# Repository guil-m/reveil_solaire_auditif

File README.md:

# Projet PCB FISE 5A POLYTECH
## Réveil solaire et auditif

### TO-DO List

- Poursuivre routing

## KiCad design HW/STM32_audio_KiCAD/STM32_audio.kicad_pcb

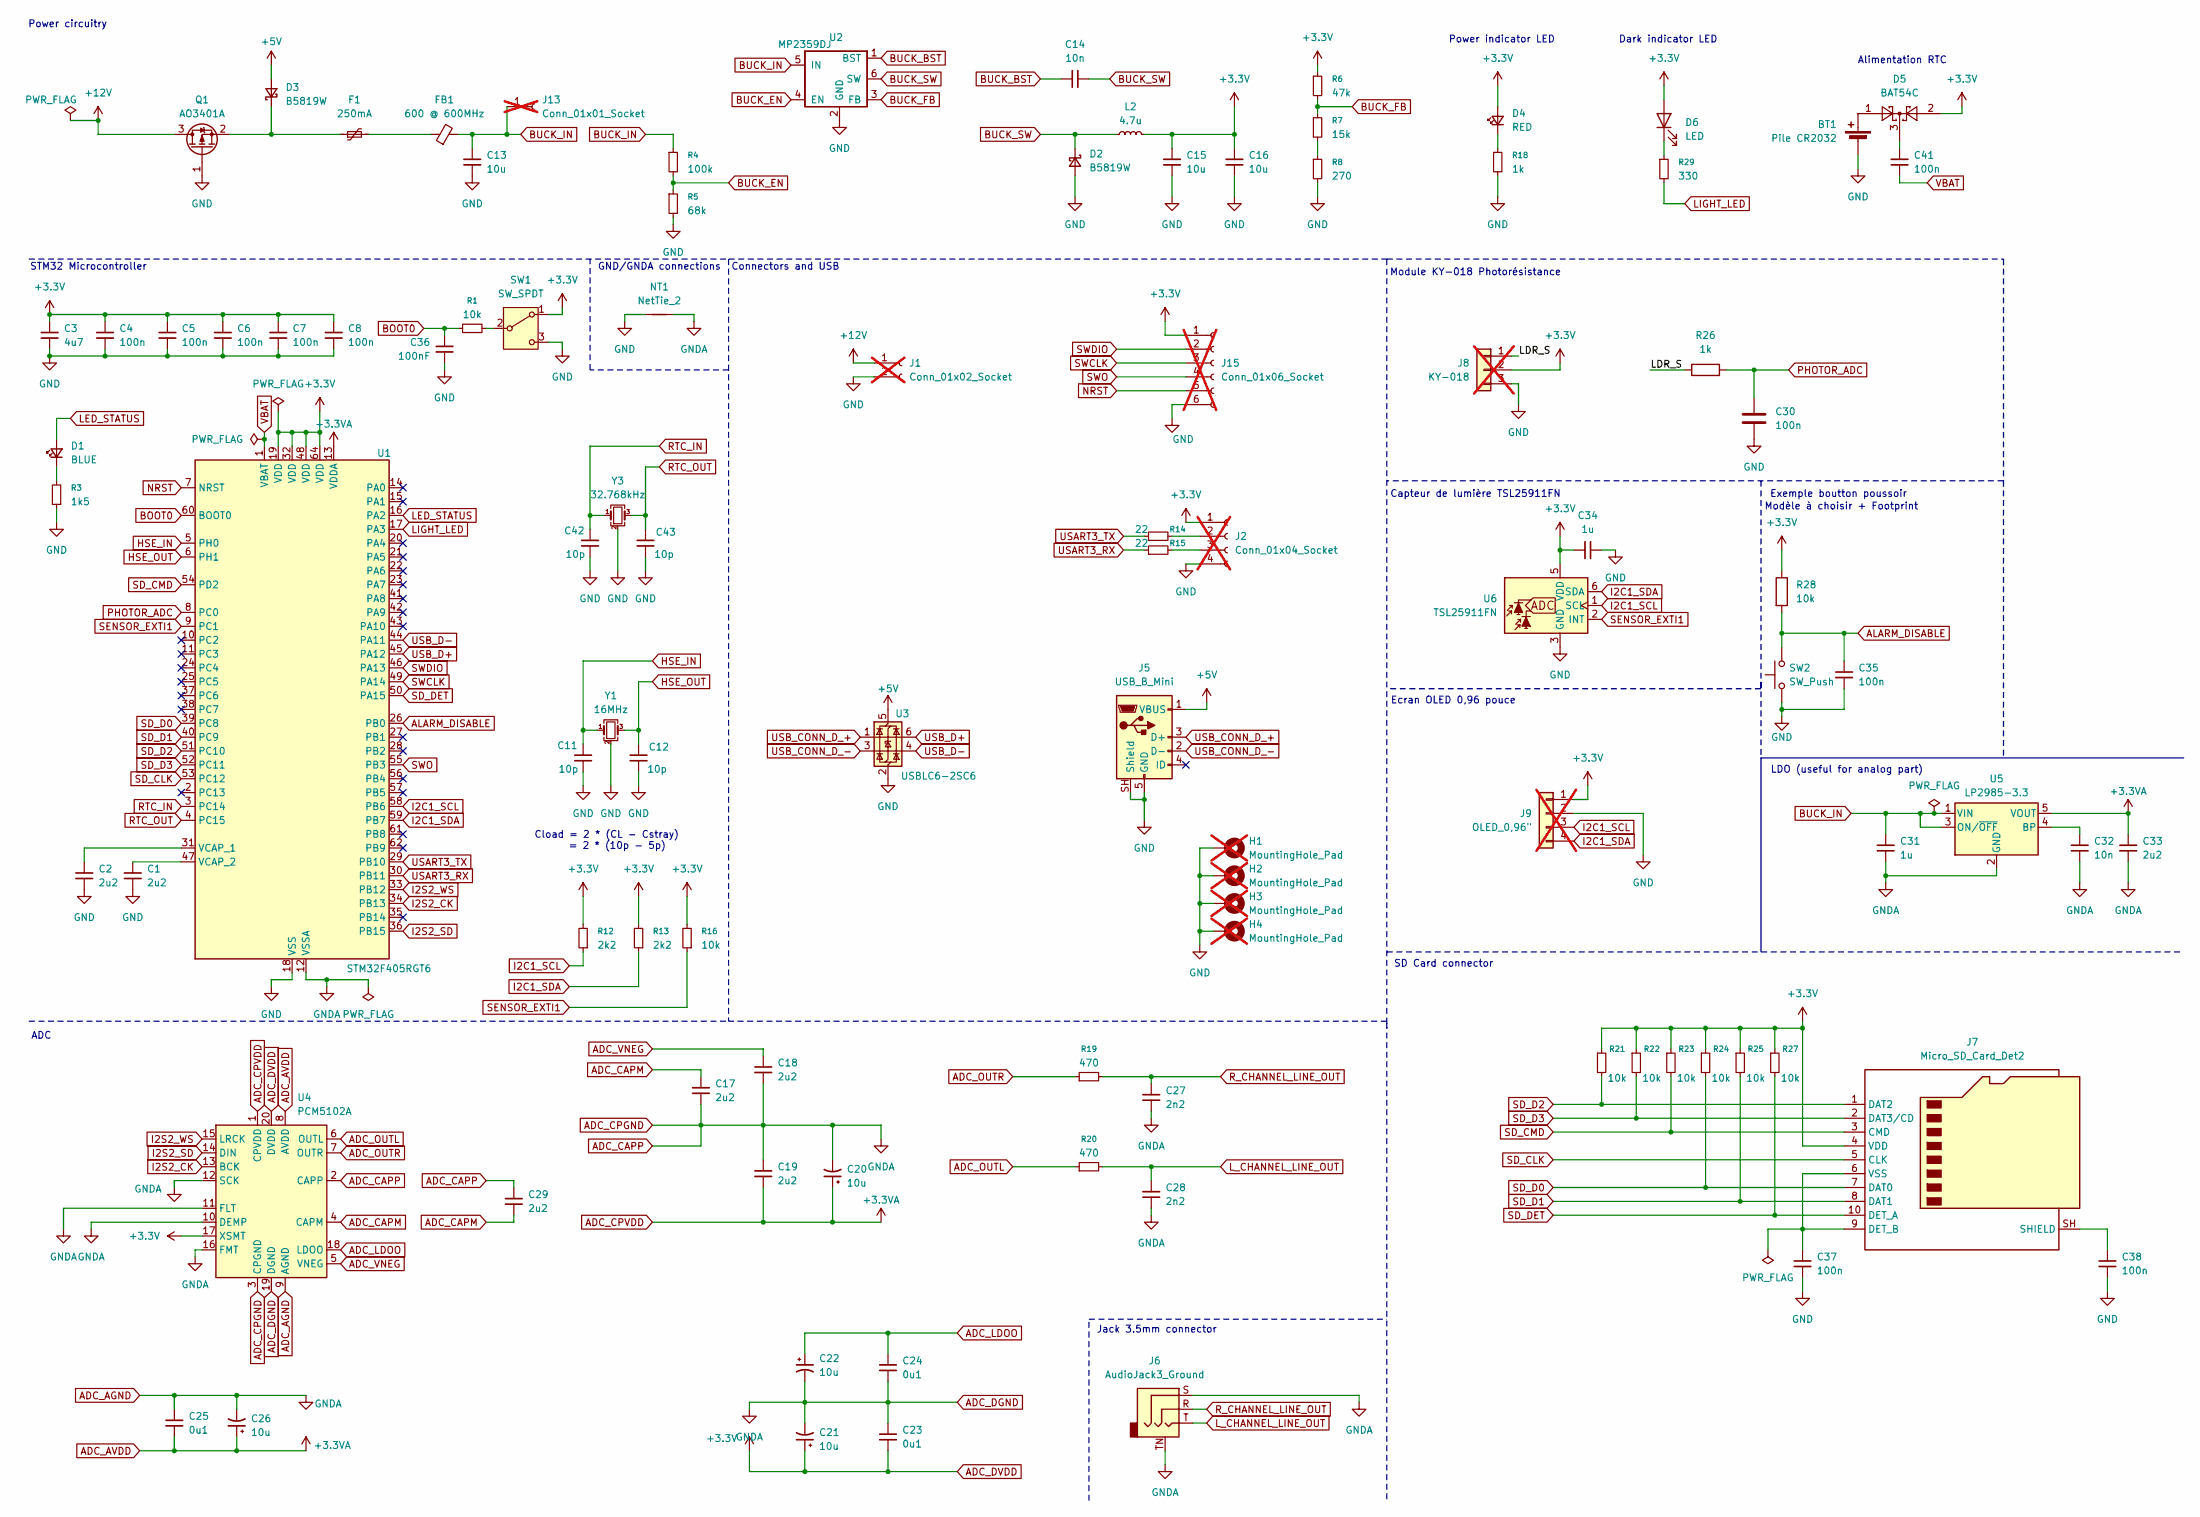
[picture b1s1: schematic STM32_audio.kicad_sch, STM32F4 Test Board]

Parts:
BT1: Pile CR2032; BatteryHolder_Keystone_1060_1x2032; LCSC Part # C238069
C1, C2: 2u2; C_0603_1608Metric; LCSC Part # C23630
C3: 4u7; C_0603_1608Metric; LCSC Part # C19666
C4, C5, C6, C7, C8, C30, C35, C37, C38, C41: 100n; C_0402_1005Metric; LCSC Part # C1525
C11, C12, C42, C43: 10p; C_0402_1005Metric; LCSC Part # C32949
C13, C15, C16: 10u; C_1206_3216Metric; LCSC Part # C9807
C14: 10n; C_0603_1608Metric; LCSC Part # C1589
C17, C18, C19, C29, C33: 2u2; C_0402_1005Metric; LCSC Part # C386077
C20, C21, C22, C26: 10u; C_0402_1005Metric; LCSC Part # C15525
C23, C24, C25: 0u1; C_0402_1005Metric; LCSC Part # C1525
C27, C28: 2n2; C_0402_1005Metric; LCSC Part # C1531
C31, C34: 1u; C_0603_1608Metric; LCSC Part # C1592
C32: 10n; C_0402_1005Metric; LCSC Part # C15195
C36: 100nF; C_0402_1005Metric; LCSC Part # C1525
D1: BLUE; LED_0603_1608Metric; LCSC Part # C2288
D2, D3: B5819W; D_SOD-123; LCSC Part # C8598
D4: RED; LED_0603_1608Metric; LCSC Part # C2286
D5: BAT54C; SOT-23; LCSC Part # C2135
D6: LED; LED_0603_1608Metric; LCSC Part # C2289
F1: 250mA; Fuse_1206_3216Metric; LCSC Part # C70075
FB1: 600 @ 600MHz; L_0805_2012Metric; LCSC Part # C1017
H1, H2, H3, H4: MountingHole_Pad; MountingHole_2.2mm_M2_Pad_Via; not fitted
J1: Conn_01x02_Socket; PinHeader_1x02_P2.54mm_Vertical; not fitted
J2: Conn_01x04_Socket; PinHeader_1x04_P2.54mm_Vertical; not fitted
J5: USB_B_Mini; USB_Micro-B_Molex-105017-0001; LCSC Part # C136000
J6: AudioJack3_Ground; Jack_3.5mm_CUI_SJ-3524-SMT_Horizontal; LCSC Part # C20182907
J7: Micro_SD_Card_Det2; microSD_HC_Hirose_DM3D-SF; LCSC Part # C719027
J8: KY-018; PinSocket_1x03_P2.54mm_Vertical; not fitted
J9: OLED_0,96"; PinSocket_1x04_P2.54mm_Vertical; not fitted
J13: Conn_01x01_Socket; PinSocket_1x01_P2.54mm_Vertical; not fitted
J15: Conn_01x06_Socket; PinHeader_1x06_P2.54mm_Vertical; not fitted
L2: 4.7u; L_Sunlord_SWPA3015S; LCSC Part # C19398
NT1: NetTie_2; NetTie-2_SMD_Pad2.0mm
Q1: AO3401A; SOT-23; LCSC Part # C15127
R1, R16, R21, R22, R23, R24, R25, R27: 10k; R_0402_1005Metric; LCSC Part # C25744
R3: 1k5; R_0603_1608Metric; LCSC Part # C22843
R4: 100k; R_0603_1608Metric; LCSC Part # C25803
R5: 68k; R_0603_1608Metric; LCSC Part # C23231
R6: 47k; R_0603_1608Metric; LCSC Part # C25819
R7: 15k; R_0603_1608Metric; LCSC Part # C22809
R8: 270; R_0603_1608Metric; LCSC Part # C22966
R12, R13: 2k2; R_0402_1005Metric; LCSC Part # C25879
R14, R15: 22; R_0603_1608Metric; LCSC Part # C23345
R18: 1k; R_0402_1005Metric; LCSC Part # C11702
R19, R20: 470; R_0603_1608Metric; LCSC Part # C23179
R26: 1k; R_0805_2012Metric; LCSC Part # C17513
R28: 10k; R_0805_2012Metric; LCSC Part # C17414
R29: 330; R_0402_1005Metric; LCSC Part # C25104
SW1: SW_SPDT; SW_SPDT_PCM12; LCSC Part # C963206
SW2: SW_Push; SW_Push_1P1T_NO_CK_KSC6xxG; LCSC Part # C2837531
U1: STM32F405RGT6; LQFP-64_10x10mm_P0.5mm; LCSC Part # C15742
U2: MP2359DJ; SOT-23-6; LCSC Part # C30197555
U3: USBLC6-2SC6; SOT-23-6; LCSC Part # C7519
U4: PCM5102A; TSSOP-20_4.4x6.5mm_P0.65mm; LCSC Part # C107671
U5: LP2985-3.3; SOT-23-5; LCSC Part # C95414
U6: TSL25911FN; AMS_TSL25911FN; LCSC Part # C176812
Y1: 16MHz; Crystal_SMD_3225-4Pin_3.2x2.5mm; LCSC Part # C13738
Y3: 32.768kHz; Crystal_SMD_3225-4Pin_3.2x2.5mm; LCSC Part # C5280579

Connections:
+5V: D3.2 (A), J5.1 (VBUS), U3.5 (VBUS)
+12V: J1.1, Q1.3 (D)
/LDR_S: J8.1, R26.1
ADC_AGND: C17.2, C18.2, C19.1, C20.2, C21.2, C22.2, C23.1, C24.2, C25.1, C26.2, C27.2, C28.2, C29.1, C31.2, C32.2, C33.2, J6.S, J6.TN, NT1.2, U1.12 (VSSA), U4.2 (CAPP), U4.3 (CPGND), U4.9 (AGND), U4.10 (DEMP), U4.11 (FLT), U4.12 (SCK), U4.16 (FMT), U4.19 (DGND), U5.2 (GND)
ADC_AVDD: C19.2, C20.1, C25.2, C26.1, C33.1, U1.13 (VDDA), U4.1 (CPVDD), U4.8 (AVDD), U5.5 (VOUT); also elsewhere on the board
ADC_CAPM: C17.1, C29.2, U4.4 (CAPM)
ADC_DVDD: C3.1, C4.1, C5.1, C6.1, C7.1, C8.1, C15.2, C16.2, C21.1, C23.2, C34.1, D4.2 (A), D5.2, D6.2 (A), J2.1, J7.4 (VDD), J8.2, J9.1, J15.1, L2.2, R6.1, R12.2, R13.2, R16.2, R21.1, R22.1, R23.1, R24.1, R25.1, R27.1, R28.1, SW1.1 (A), U1.19 (VDD), U1.32 (VDD), U1.48 (VDD), U1.64 (VDD), U4.17 (XSMT), U4.20 (DVDD), U6.5 (VDD)
ADC_LDOO: C22.1, C24.1, U4.18 (LDOO)
ADC_OUTL: R20.1, U4.6 (OUTL)
ADC_OUTR: R19.1, U4.7 (OUTR)
ADC_VNEG: C18.1, U4.5 (VNEG)
ALARM_DISABLE: C35.1, R28.2, SW2.2, U1.26 (PB0)
BOOT0: C36.1, R1.1, U1.60 (BOOT0)
BUCK_BST: C14.1, U2.1 (BST)
BUCK_EN: R4.2, R5.1, U2.4 (EN)
BUCK_FB: R6.2, R7.1, U2.3 (FB)
BUCK_IN: C13.1, C31.1, FB1.2, J13.1 (Pin_1_1), R4.1, U2.5 (IN), U5.1 (VIN), U5.3 (ON/~OFF)
BUCK_SW: C14.2, D2.1 (K), L2.1, U2.6 (SW)
GND: BT1.2 (-), C1.2, C2.2, C3.2, C4.2, C5.2, C6.2, C7.2, C8.2, C11.2, C12.2, C13.2, C15.1, C16.1, C30.2, C34.2, C35.2, C36.2, C37.2, C38.2, C42.2, C43.2, D2.2 (A), H1.1 (1_1), H2.1 (1_1), H3.1 (1_1), H4.1 (1_1), J1.2, J2.4, J5.5 (GND), J5.SH (Shield), J8.3, J9.2, J15.6, NT1.1, Q1.1 (G), R3.1, R5.2, R8.2, R18.2, SW1.3 (C), SW2.1, U1.18 (VSS), U1.63 (VSS), U2.2 (GND), U3.2 (GND), U6.3 (GND), Y1.2 (G), Y1.4 (G), Y3.2 (G), Y3.4 (G)
HSE_IN: C11.1, U1.5 (PH0), Y1.1
HSE_OUT: C12.1, U1.6 (PH1), Y1.3
I2C1_SCL: J9.3, R12.1, U1.58 (PB6), U6.1 (SCL)
I2C1_SDA: J9.4, R13.1, U1.59 (PB7), U6.6 (SDA)
I2S2_CK: U1.34 (PB13), U4.13 (BCK)
I2S2_SD: U1.36 (PB15), U4.14 (DIN)
I2S2_WS: U1.33 (PB12), U4.15 (LRCK)
LED_STATUS: D1.2 (A), U1.16 (PA2)
LIGHT_LED: R29.2, U1.17 (PA3)
L_CHANNEL_LINE_OUT: C28.1, J6.T, R20.2
NRST: J15.5, U1.7 (NRST)
unnamed: BT1.1 (+), D5.1
unnamed: C41.1, D5.3
unnamed: D1.1 (K), R3.2
unnamed: D3.1 (K), F1.1, Q1.2 (S)
unnamed: D4.1 (K), R18.1
unnamed: D6.1 (K), R29.1
unnamed: F1.2, FB1.1
unnamed: J2.2, R14.2
unnamed: J2.3, R15.2
unnamed: C37.1, J7.6 (VSS), J7.9 (DET_B)
unnamed: C38.1, J7.SH (SHIELD)
unnamed: R7.2, R8.1
unnamed: R1.2, SW1.2 (B)
unnamed: C2.1, U1.31 (VCAP_1)
unnamed: C1.1, U1.47 (VCAP_2)
unnamed: C32.1, U5.4 (BP)
PHOTOR_ADC: C30.1, R26.2, U1.8 (PC0)
RTC_IN: C42.1, U1.3 (PC14), Y3.1
RTC_OUT: C43.1, U1.4 (PC15), Y3.3
R_CHANNEL_LINE_OUT: C27.1, J6.R, R19.2
SD_CLK: J7.5 (CLK), U1.53 (PC12)
SD_CMD: J7.3 (CMD), R23.2, U1.54 (PD2)
SD_D0: J7.7 (DAT0), R24.2, U1.39 (PC8)
SD_D1: J7.8 (DAT1), R25.2, U1.40 (PC9)
SD_D2: J7.1 (DAT2), R21.2, U1.51 (PC10)
SD_D3: J7.2 (DAT3/CD), R22.2, U1.52 (PC11)
SD_DET: J7.10 (DET_A), R27.2, U1.50 (PA15)
SENSOR_EXTI1: R16.1, U1.9 (PC1), U6.2 (INT)
SWCLK: J15.3, U1.49 (PA14)
SWDIO: J15.2, U1.46 (PA13)
SWO: J15.4, U1.55 (PB3)
USART3_RX: R15.1, U1.30 (PB11)
USART3_TX: R14.1, U1.29 (PB10)
USB_CONN_D_+: J5.3 (D+), U3.1 (I/O1)
USB_CONN_D_-: J5.2 (D-), U3.3 (I/O2)
USB_D+: U1.45 (PA12), U3.6 (I/O1)
USB_D-: U1.44 (PA11), U3.4 (I/O2)
VBAT: C41.2, U1.1 (VBAT)

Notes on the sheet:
GND/GNDA connections
Module KY-018 Photorésistance
Power circuitry
Jack 3.5mm connector
Cload = 2 * (CL - Cstray) = 2 * (10p - 5p)
STM32 Microcontroller
Alimentation RTC
ADC
Capteur de lumière TSL25911FN
Exemple boutton poussoir
LDO (useful for analog part)
Modèle à choisir + Footprint
Power indicator LED
Connectors and USB
Ecran OLED 0,96 pouce
Dark indicator LED
SD Card connector

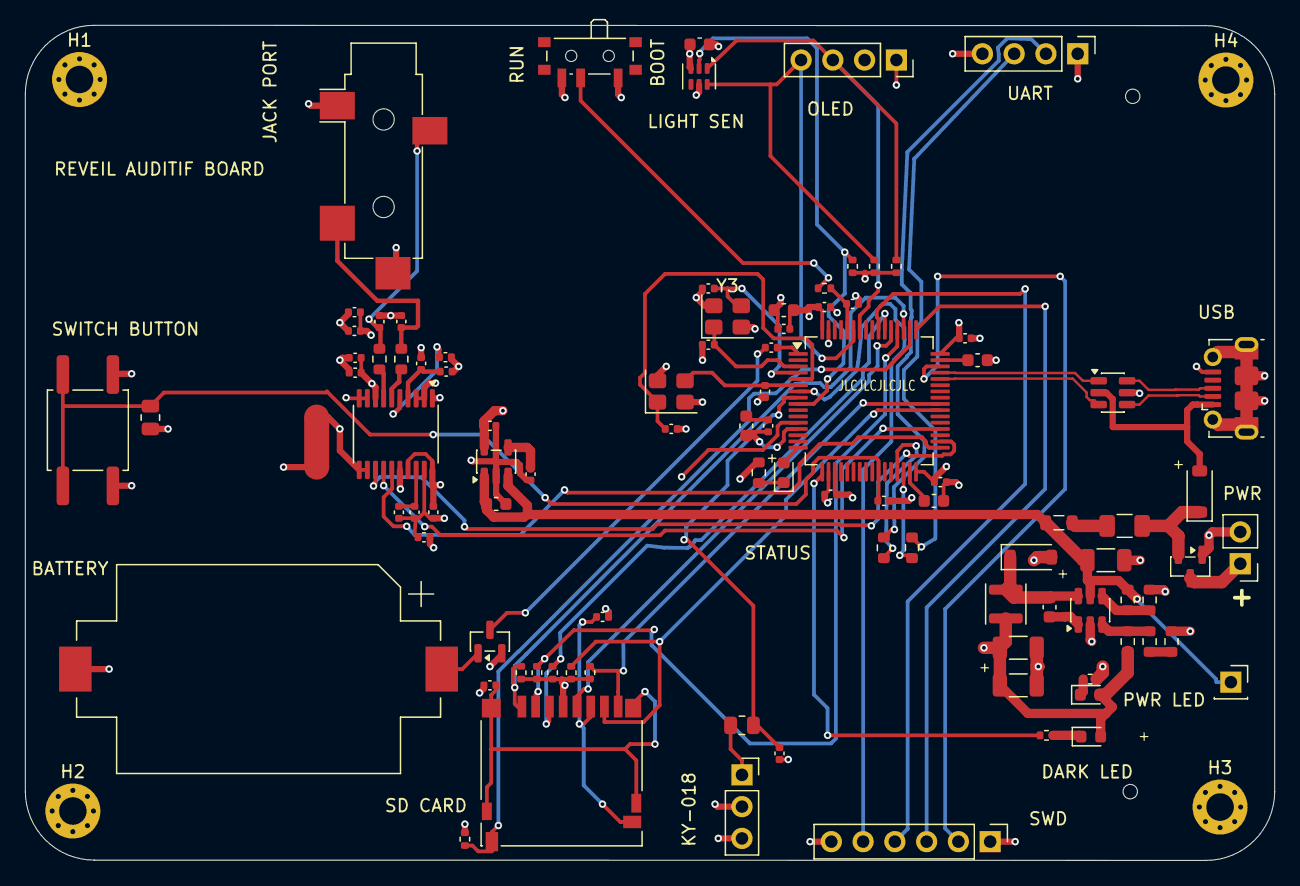
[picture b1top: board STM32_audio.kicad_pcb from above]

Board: 4 copper layers, 99.9 x 66.8 mm, 100 parts (0 on the bottom side), 69 nets.

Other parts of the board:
C9: 1u; C_0603_1608Metric
C10: 10n; C_0402_1005Metric

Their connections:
ADC_AVDD: C9.1, C10.1; also elsewhere on the board
ADC_DGND: C9.2, C10.2

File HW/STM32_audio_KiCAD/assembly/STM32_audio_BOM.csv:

"Reference","Qty","Value","DNP","Exclude from BOM","Exclude from Board","Exclude from Simulation","Exclude from Position Files","Footprint","Datasheet","LCSC Part #"
"BT1","1","Pile CR2032","","","","","${EXCLUDE_FROM_POS_FILES}","Battery:BatteryHolder_Keystone_1060_1x2032","","C22363833"
"C1,C2","2","2u2","","","","","${EXCLUDE_FROM_POS_FILES}","Capacitor_SMD:C_0603_1608Metric","","C23630"
"C3","1","4u7","","","","","${EXCLUDE_FROM_POS_FILES}","Capacitor_SMD:C_0603_1608Metric","","C19666"
"C4,C5,C6,C7,C8,C30,C35,C37,C38,C41","10","100n","","","","","${EXCLUDE_FROM_POS_FILES}","Capacitor_SMD:C_0402_1005Metric","","C1525"
"C11,C12,C42,C43","4","10p","","","","","${EXCLUDE_FROM_POS_FILES}","Capacitor_SMD:C_0402_1005Metric","","C32949"
"C13,C15,C16","3","10u","","","","","${EXCLUDE_FROM_POS_FILES}","Capacitor_SMD:C_1206_3216Metric","","C9807"
"C14","1","10n","","","","","${EXCLUDE_FROM_POS_FILES}","Capacitor_SMD:C_0603_1608Metric","","C1589"
"C17,C18,C19,C29,C33","5","2u2","","","","","${EXCLUDE_FROM_POS_FILES}","Capacitor_SMD:C_0402_1005Metric","","C386077"
"C20,C21,C22,C26","4","10u","","","","","${EXCLUDE_FROM_POS_FILES}","Capacitor_SMD:C_0402_1005Metric","","C15525"
"C23,C24,C25","3","0u1","","","","","${EXCLUDE_FROM_POS_FILES}","Capacitor_SMD:C_0402_1005Metric","","C1525"
"C27,C28","2","2n2","","","","","${EXCLUDE_FROM_POS_FILES}","Capacitor_SMD:C_0402_1005Metric","","C1531"
"C31,C34","2","1u","","","","","${EXCLUDE_FROM_POS_FILES}","Capacitor_SMD:C_0603_1608Metric","","C1592"
"C32","1","10n","","","","","${EXCLUDE_FROM_POS_FILES}","Capacitor_SMD:C_0402_1005Metric","","C15195"
"C36","1","100nF","","","","","${EXCLUDE_FROM_POS_FILES}","Capacitor_SMD:C_0402_1005Metric","","C1525"
"D1","1","BLUE","","","","","${EXCLUDE_FROM_POS_FILES}","LED_SMD:LED_0603_1608Metric","","C2288"
"D2,D3","2","B5819W","","","","","${EXCLUDE_FROM_POS_FILES}","Diode_SMD:D_SOD-123","","C8598"
"D4","1","RED","","","","","${EXCLUDE_FROM_POS_FILES}","LED_SMD:LED_0603_1608Metric","","C2286"
"D5","1","BAT54C","","","","","${EXCLUDE_FROM_POS_FILES}","Package_TO_SOT_SMD:SOT-23","http://www.diodes.com/_files/datasheets/ds11005.pdf","C2135"
"D6","1","LED","","","","","${EXCLUDE_FROM_POS_FILES}","LED_SMD:LED_0603_1608Metric","","C2289"
"F1","1","250mA","","","","","${EXCLUDE_FROM_POS_FILES}","Fuse:Fuse_1206_3216Metric","","C70075"
"FB1","1","600 @ 600MHz","","","","","${EXCLUDE_FROM_POS_FILES}","Inductor_SMD:L_0805_2012Metric","","C1017"
"J5","1","USB_B_Mini","","","","","${EXCLUDE_FROM_POS_FILES}","Connector_USB:USB_Micro-B_Molex-105017-0001","","C136000"
"J6","1","AudioJack3_Ground","","","","","${EXCLUDE_FROM_POS_FILES}","Connector_Audio:Jack_3.5mm_CUI_SJ-3524-SMT_Horizontal","","C20182907"
"J7","1","Micro_SD_Card_Det2","","","","","${EXCLUDE_FROM_POS_FILES}","Connector_Card:microSD_HC_Hirose_DM3D-SF","https://www.hirose.com/en/product/document?clcode=&productna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","C719027"
"L2","1","4.7u","","","","","${EXCLUDE_FROM_POS_FILES}","Inductor_SMD:L_Sunlord_SWPA3015S","","C19398"
"Q1","1","AO3401A","","","","","${EXCLUDE_FROM_POS_FILES}","Package_TO_SOT_SMD:SOT-23","http://www.aosmd.com/pdfs/datasheet/AO3401A.pdf","C15127"
"R1,R16,R21,R22,R23,R24,R25,R27","8","10k","","","","","${EXCLUDE_FROM_POS_FILES}","Resistor_SMD:R_0402_1005Metric","","C25744"
"R3","1","1k5","","","","","${EXCLUDE_FROM_POS_FILES}","Resistor_SMD:R_0603_1608Metric","","C22843"
"R4","1","100k","","","","","${EXCLUDE_FROM_POS_FILES}","Resistor_SMD:R_0603_1608Metric","","C25803"
"R5","1","68k","","","","","${EXCLUDE_FROM_POS_FILES}","Resistor_SMD:R_0603_1608Metric","","C23231"
"R6","1","47k","","","","","${EXCLUDE_FROM_POS_FILES}","Resistor_SMD:R_0603_1608Metric","","C25819"
"R7","1","15k","","","","","${EXCLUDE_FROM_POS_FILES}","Resistor_SMD:R_0603_1608Metric","","C22809"
"R8","1","270","","","","","${EXCLUDE_FROM_POS_FILES}","Resistor_SMD:R_0603_1608Metric","","C22966"
"R12,R13","2","2k2","","","","","${EXCLUDE_FROM_POS_FILES}","Resistor_SMD:R_0402_1005Metric","","C25879"
"R14,R15","2","22","","","","","${EXCLUDE_FROM_POS_FILES}","Resistor_SMD:R_0603_1608Metric","","C23345"
"R18","1","1k","","","","","${EXCLUDE_FROM_POS_FILES}","Resistor_SMD:R_0402_1005Metric","","C11702"
"R19,R20","2","470","","","","","${EXCLUDE_FROM_POS_FILES}","Resistor_SMD:R_0603_1608Metric","","C23179"
"R26","1","1k","","","","","${EXCLUDE_FROM_POS_FILES}","Resistor_SMD:R_0805_2012Metric","","C17513"
"R28","1","10k","","","","","${EXCLUDE_FROM_POS_FILES}","Resistor_SMD:R_0805_2012Metric","","C17414"
"R29","1","330","","","","","${EXCLUDE_FROM_POS_FILES}","Resistor_SMD:R_0402_1005Metric","","C25104"
"SW1","1","SW_SPDT","","","","","${EXCLUDE_FROM_POS_FILES}","Button_Switch_SMD:SW_SPDT_PCM12","","C221841"
"SW2","1","SW_Push","","","","","${EXCLUDE_FROM_POS_FILES}","Button_Switch_SMD:SW_Push_1P1T_NO_CK_KSC6xxG","","C2837531"
"U1","1","STM32F405RGT6","","","","","${EXCLUDE_FROM_POS_FILES}","Package_QFP:LQFP-64_10x10mm_P0.5mm","https://www.st.com/resource/en/datasheet/stm32f405rg.pdf","C15742"
"U2","1","MP2359DJ","","","","","${EXCLUDE_FROM_POS_FILES}","Package_TO_SOT_SMD:SOT-23-6","","C14259"
"U3","1","USBLC6-2SC6","","","","","${EXCLUDE_FROM_POS_FILES}","Package_TO_SOT_SMD:SOT-23-6","https://www.st.com/resource/en/datasheet/usblc6-2.pdf","C7519"
"U4","1","PCM5102A","","","","","${EXCLUDE_FROM_POS_FILES}","Package_SO:TSSOP-20_4.4x6.5mm_P0.65mm","https://www.ti.com/lit/ds/symlink/pcm5102a.pdf","C107671"
"U5","1","LP2985-3.3","","","","","${EXCLUDE_FROM_POS_FILES}","Package_TO_SOT_SMD:SOT-23-5","http://www.ti.com/lit/ds/symlink/lp2985.pdf","C95414"
"U6","1","TSL25911FN","","","","","${EXCLUDE_FROM_POS_FILES}","OptoDevice:AMS_TSL25911FN","https://ams.com/documents/20143/9331680/TSL2591_DS000338_7-00.pdf","C176812"
"Y1","1","16MHz","","","","","${EXCLUDE_FROM_POS_FILES}","Crystal:Crystal_SMD_3225-4Pin_3.2x2.5mm","","C13738"
"Y3","1","32.768kHz","","","","","${EXCLUDE_FROM_POS_FILES}","Crystal:Crystal_SMD_3225-4Pin_3.2x2.5mm","","C5280579"

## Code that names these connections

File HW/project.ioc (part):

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Mcu.Name=STM32F405RGTx
Mcu.Package=LQFP64
Mcu.UserName=STM32F405RGTx
PA11.Mode=Device_Only
PA11.Signal=USB_OTG_FS_DM
PA12.Mode=Device_Only
PA12.Signal=USB_OTG_FS_DP
PA13.Mode=Trace_Asynchronous_SW
PA13.Signal=SYS_JTMS-SWDIO
PA14.Mode=Trace_Asynchronous_SW
PA14.Signal=SYS_JTCK-SWCLK
PA15.GPIOParameters=GPIO_Label
PA15.GPIO_Label=DSIO_DET
PA15.Signal=GPIO_Input
PA2.GPIOParameters=GPIO_Label
PA2.GPIO_Label=LED_STATUS
PA2.Signal=GPIO_Output
PA3.GPIOParameters=PinState,GPIO_Label
PA3.GPIO_Label=LIGHT_LED
PA3.PinState=GPIO_PIN_SET
PA3.Signal=GPIO_Output
PB0.GPIOParameters=GPIO_Label,GPIO_ModeDefaultEXTI
PB0.GPIO_Label=ALARM_DISABLE
PB0.GPIO_ModeDefaultEXTI=GPIO_MODE_IT_FALLING
PB0.Signal=GPXTI0
PB10.Mode=Asynchronous
PB10.Signal=USART3_TX
PB11.Mode=Asynchronous
PB11.Signal=USART3_RX
PB12.Mode=Half_Duplex_Master
PB12.Signal=I2S2_WS
PB13.Mode=Half_Duplex_Master
PB13.Signal=I2S2_CK
PB15.Mode=Half_Duplex_Master
PB15.Signal=I2S2_SD
PB3.Mode=Trace_Asynchronous_SW
PB3.Signal=SYS_JTDO-SWO
PB6.Mode=I2C
PB6.Signal=I2C1_SCL
PB7.Mode=I2C
PB7.Signal=I2C1_SDA
PC0.GPIOParameters=GPIO_Label
PC0.GPIO_Label=PHOTOR_ADC
PC0.Signal=ADCx_IN10
PC1.GPIOParameters=GPIO_Label
PC1.GPIO_Label=SENSOR_EXTI1
PC1.Signal=GPXTI1
PC10.GPIOParameters=GPIO_Speed_High_Default
PC10.GPIO_Speed_High_Default=GPIO_SPEED_FREQ_LOW
PC10.Mode=SD_4_bits_Wide_bus
PC10.Signal=SDIO_D2
PC11.GPIOParameters=GPIO_Speed_High_Default
PC11.GPIO_Speed_High_Default=GPIO_SPEED_FREQ_LOW
PC11.Mode=SD_4_bits_Wide_bus
PC11.Signal=SDIO_D3
PC12.GPIOParameters=GPIO_Speed_High_Default
PC12.GPIO_Speed_High_Default=GPIO_SPEED_FREQ_LOW
PC12.Mode=SD_4_bits_Wide_bus
PC12.Signal=SDIO_CK
PC14-OSC32_IN.GPIOParameters=GPIO_Label
PC14-OSC32_IN.GPIO_Label=RTC_IN
PC14-OSC32_IN.Mode=LSE-External-Oscillator
PC14-OSC32_IN.Signal=RCC_OSC32_IN
PC15-OSC32_OUT.GPIOParameters=GPIO_Label
PC15-OSC32_OUT.GPIO_Label=RTC_OUT
PC15-OSC32_OUT.Mode=LSE-External-Oscillator
PC15-OSC32_OUT.Signal=RCC_OSC32_OUT
PC8.GPIOParameters=GPIO_Speed_High_Default
PC8.GPIO_Speed_High_Default=GPIO_SPEED_FREQ_LOW
PC8.Mode=SD_4_bits_Wide_bus
PC8.Signal=SDIO_D0
PC9.GPIOParameters=GPIO_Speed_High_Default
PC9.GPIO_Speed_High_Default=GPIO_SPEED_FREQ_LOW
PC9.Mode=SD_4_bits_Wide_bus
PC9.Signal=SDIO_D1
PD2.GPIOParameters=GPIO_Speed_High_Default
PD2.GPIO_Speed_High_Default=GPIO_SPEED_FREQ_LOW
PD2.Mode=SD_4_bits_Wide_bus
PD2.Signal=SDIO_CMD
PH0-OSC_IN.Mode=HSE-External-Oscillator
PH0-OSC_IN.Signal=RCC_OSC_IN
PH1-OSC_OUT.Mode=HSE-External-Oscillator
PH1-OSC_OUT.Signal=RCC_OSC_OUT
RCC.HSE_VALUE=16000000
RCC.SYSCLKFreq_VALUE=16000000
board=custom
